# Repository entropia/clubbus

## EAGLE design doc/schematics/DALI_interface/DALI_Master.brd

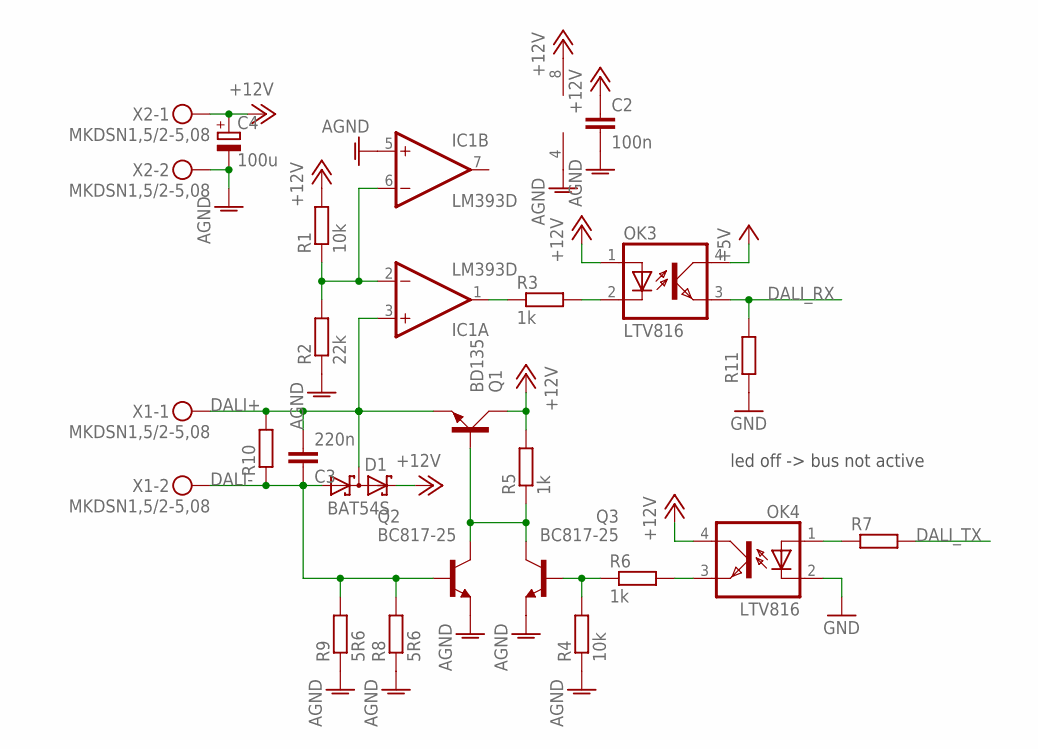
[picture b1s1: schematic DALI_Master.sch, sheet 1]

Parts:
C2: 100n; C0805
C3: 220n; C0805
C4: 100u; E2,5-6
D1: BAT54S; SOT23
IC1: LM393D; SO08
OK3, OK4: LTV816; DIL04
Q1: BD135; TO126AV
Q2, Q3: BC817-25; SOT23-BEC
R1, R4: 10k; R0805
R2: 22k; R0805
R3, R5, R6: 1k; R0805
R7, R10, R11: R-EU_R0805; R0805
R8, R9: 5R6; R1206
X1, X2: MKDSN1,5/2-5,08

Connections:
+5V: OK3.4 (COL); also elsewhere on the board
+12V: C2.1, C4.+, D1.2 (C2), IC1.8 (V+), OK3.1 (A), OK4.4 (COL), Q1.C, R1.2, R5.2, X2.1
AGND: C2.2, C4.-, IC1.4 (V-), IC1.5 (+IN), Q2.E, Q3.E, R2.1, R4.1, R8.1, R9.1, X2.2
DALI+: C3.2, D1.3 (C1A2), IC1.3 (+IN), Q1.E, R10.2, X1.1
DALI-: C3.1, D1.1 (A1), Q2.B, R8.2, R9.2, R10.1, X1.2
DALI_RX: OK3.3 (EMIT), R11.2; also elsewhere on the board
DALI_TX: R7.2; also elsewhere on the board
GND: OK4.2 (C), R11.1; also elsewhere on the board
unnamed: IC1.1 (OUT), R3.1
unnamed: IC1.2 (-IN), IC1.6 (-IN), R1.1, R2.2
unnamed: OK3.2 (C), R3.2
unnamed: Q3.B, R4.2, R6.1
unnamed: OK4.3 (EMIT), R6.2
unnamed: Q1.B, Q2.C, Q3.C, R5.1
unnamed: OK4.1 (A), R7.1

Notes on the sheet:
led off -> bus not active

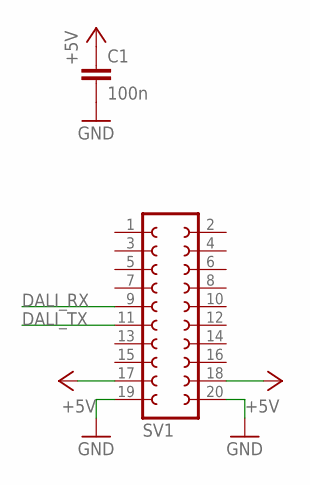
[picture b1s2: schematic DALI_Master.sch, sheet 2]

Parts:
C1: 100n; C0805
SV1: FE10-2

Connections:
+5V: C1.1, SV1.17, SV1.18; also elsewhere on the board
DALI_RX: SV1.9; also elsewhere on the board
DALI_TX: SV1.11; also elsewhere on the board
GND: C1.2, SV1.19, SV1.20; also elsewhere on the board

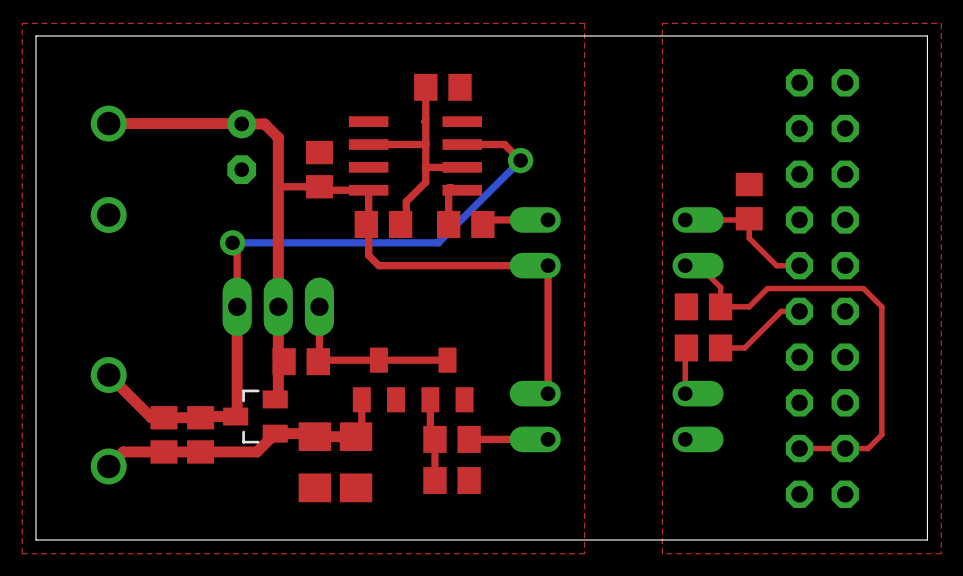
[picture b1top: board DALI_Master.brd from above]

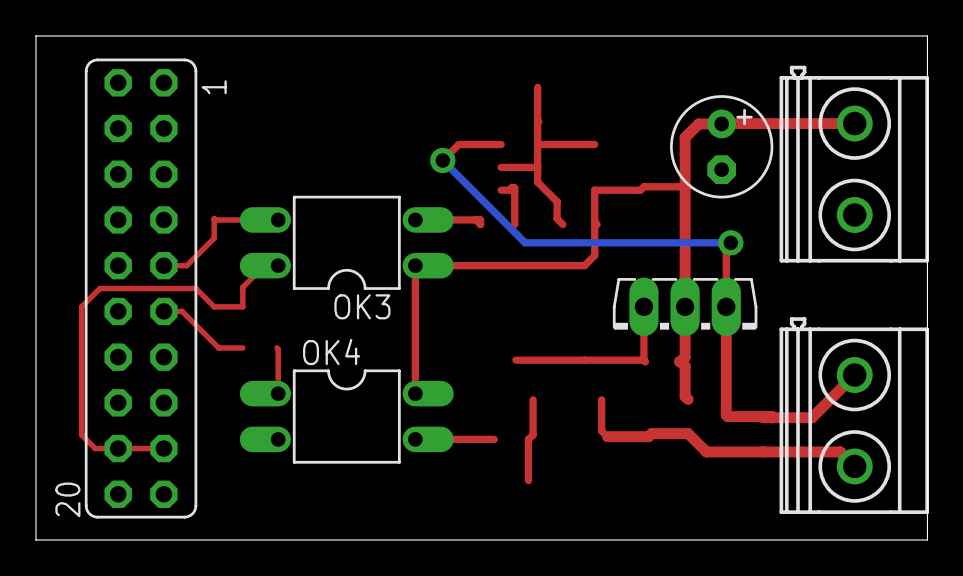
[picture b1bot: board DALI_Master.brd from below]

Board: 2 copper layers, 49.5 x 28.0 mm, 25 parts (7 on the bottom side), 15 nets.

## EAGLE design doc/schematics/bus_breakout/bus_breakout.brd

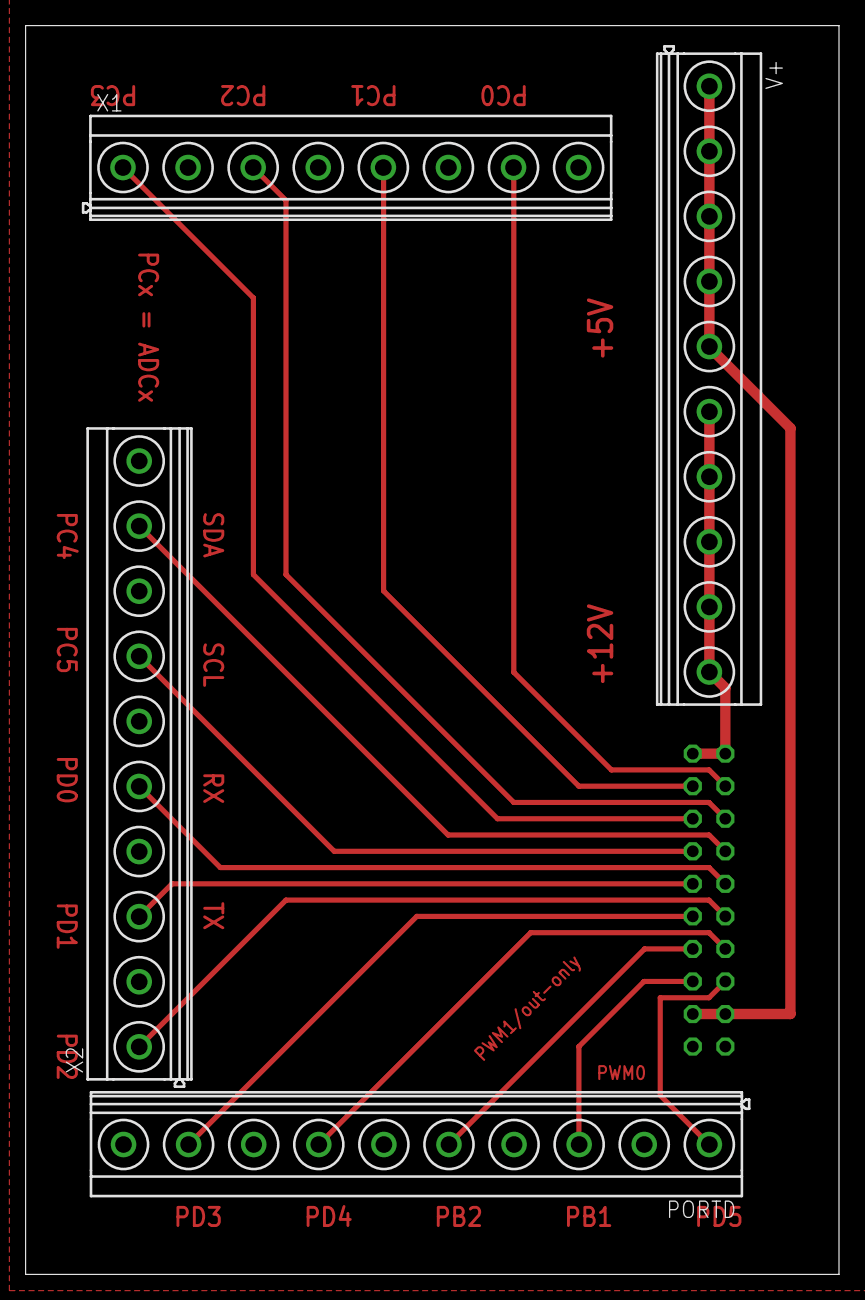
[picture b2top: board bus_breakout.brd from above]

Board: 2 copper layers, 63.5 x 97.5 mm, 5 parts (1 on the bottom side), 17 nets.

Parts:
PORTD: MKDSN1,5/10-5,08
SV2: FE10-2
V+: MKDSN1,5/10-5,08
X1: MKDSN1,5/8-5,08
X2: MKDSN1,5/10-5,08

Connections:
+5V: SV2.17, SV2.18, V+.1, V+.2, V+.3, V+.4, V+.5
+12V: SV2.1, SV2.2, V+.6, V+.7, V+.8, V+.9, V+.10
GND: PORTD.2, PORTD.4, PORTD.6, PORTD.8, PORTD.10, SV2.19, SV2.20, X1.2, X1.4, X1.6, X1.8, X2.2, X2.4, X2.6, X2.8, X2.10
PC0/ADC0: SV2.4, X1.7
PC1/ADC1: SV2.3, X1.5
PC2/ADC2: SV2.6, X1.3
PC3/ADC3: SV2.5, X1.1
PC4/ADC4/SDA: SV2.8, X2.9
PC5/ADC5/SCL: SV2.7, X2.7
PD0/RX: SV2.10, X2.5
PD1/TX: SV2.9, X2.3
PD2: SV2.12, X2.1
PD3: PORTD.9, SV2.11
PD4: PORTD.7, SV2.14
PD5: PORTD.1, SV2.16
PWM0: PORTD.3, SV2.15
PWM1: PORTD.5, SV2.13

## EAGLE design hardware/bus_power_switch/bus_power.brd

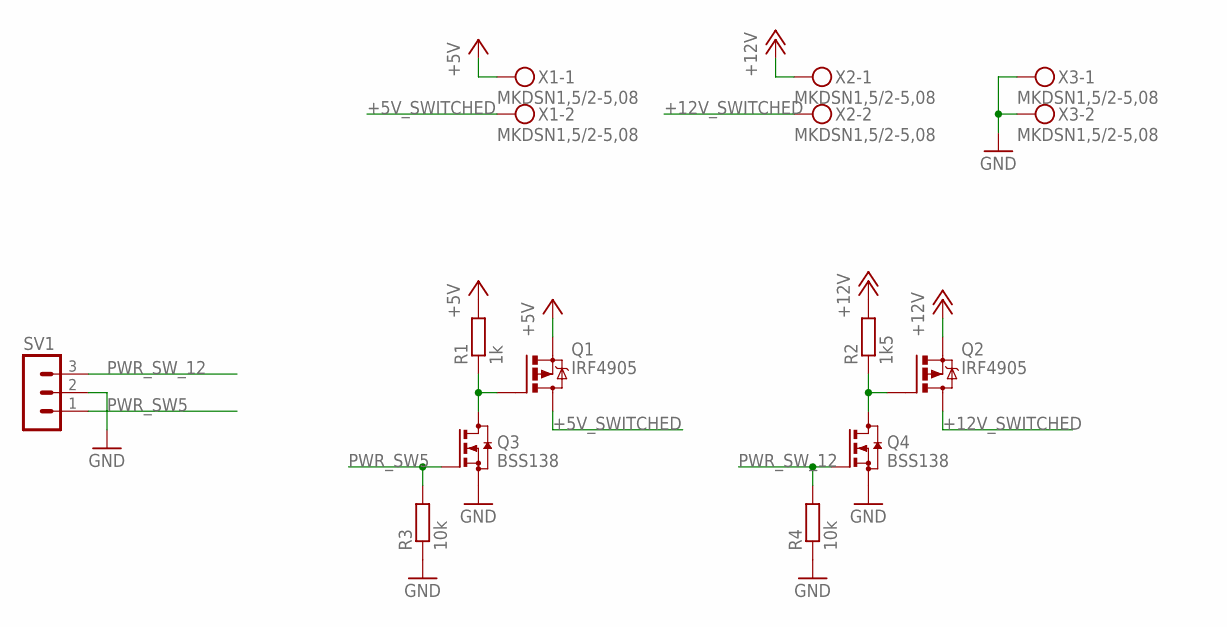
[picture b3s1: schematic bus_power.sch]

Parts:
Q1, Q2: IRF4905; TO220BV
Q3, Q4: BSS138; SOT23
R1: 1k; R0805
R2: 1k5; R0805
R3, R4: 10k; R0805
SV1: MA03-1
X1, X2, X3: MKDSN1,5/2-5,08

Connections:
+5V: Q1.S, R1.2, X1.1
+5V_SWITCHED: Q1.D, X1.2
+12V: Q2.S, R2.2, X2.1
+12V_SWITCHED: Q2.D, X2.2
G5: Q1.G, Q3.3 (D), R1.1
G12: Q2.G, Q4.3 (D), R2.1
GND: Q3.2 (S), Q4.2 (S), R3.1, R4.1, SV1.2, X3.1, X3.2
PWR_SW5: Q3.1 (G), R3.2, SV1.1
PWR_SW_12: Q4.1 (G), R4.2, SV1.3

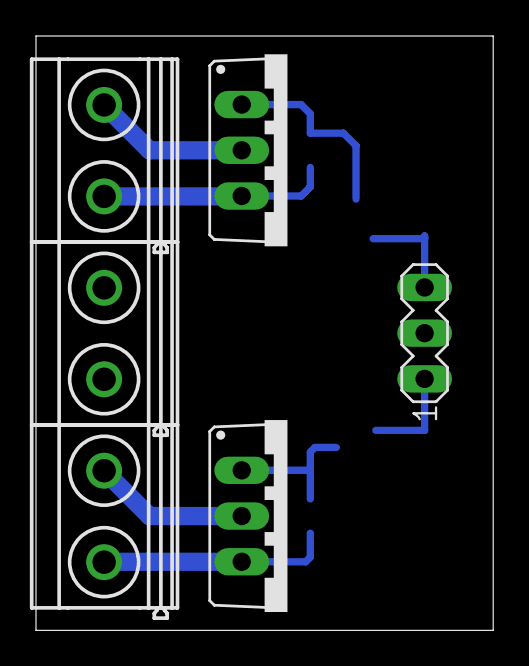
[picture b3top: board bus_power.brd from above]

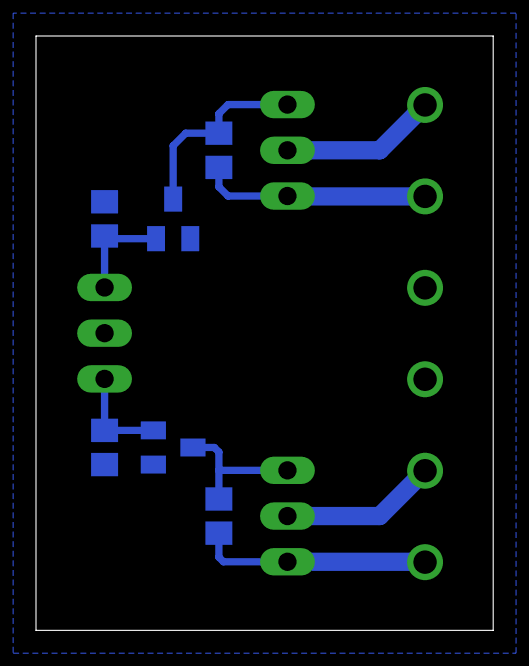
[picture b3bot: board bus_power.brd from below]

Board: 2 copper layers, 25.4 x 33.0 mm, 12 parts (6 on the bottom side), 9 nets.

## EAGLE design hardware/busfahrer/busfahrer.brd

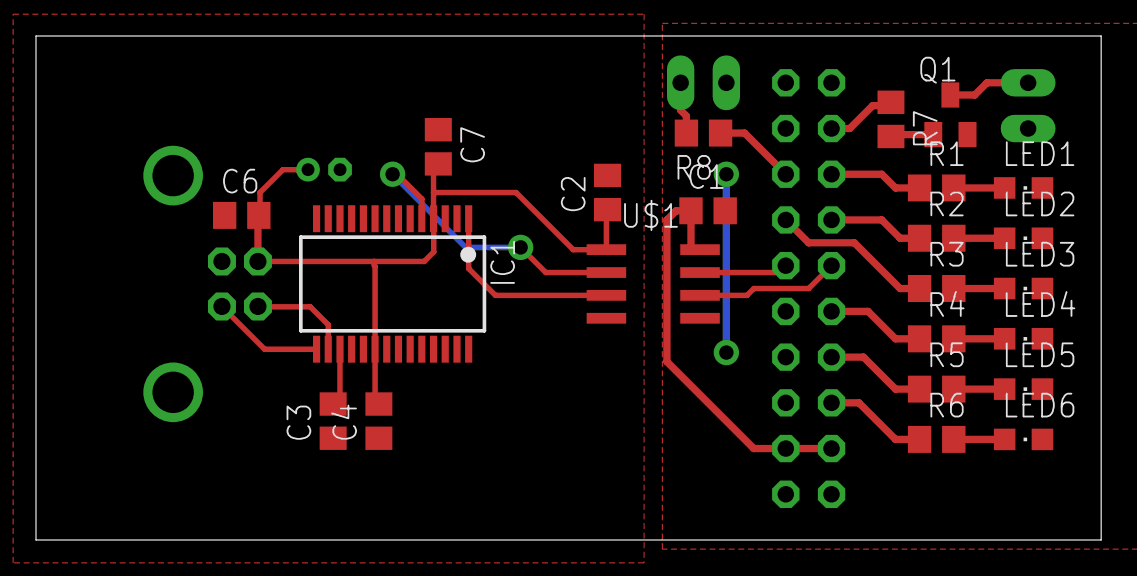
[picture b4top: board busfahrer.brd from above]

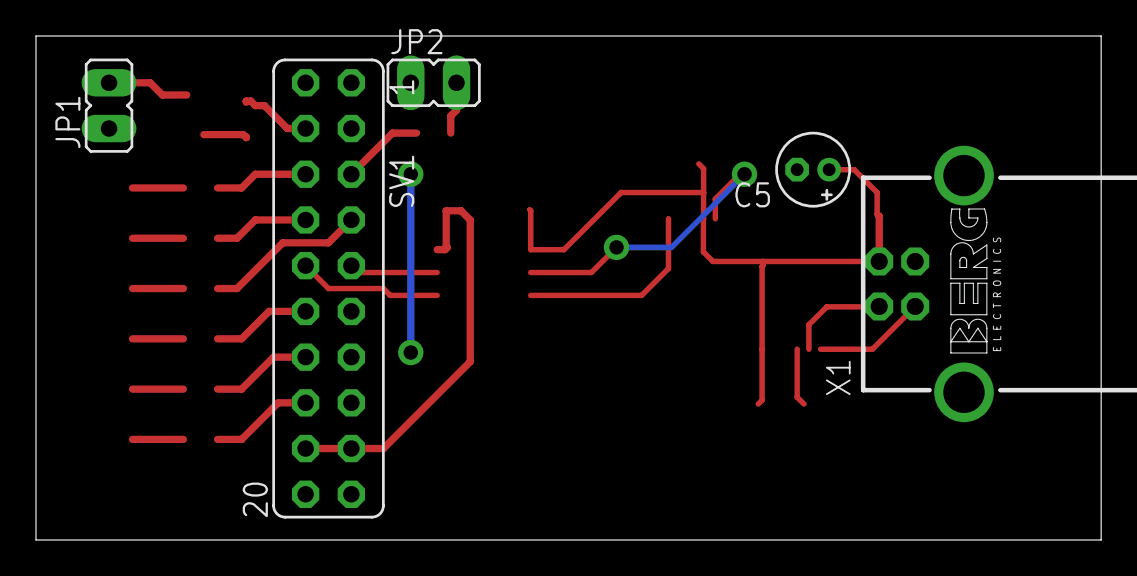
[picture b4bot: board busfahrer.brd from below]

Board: 2 copper layers, 59.2 x 28.0 mm, 28 parts (5 on the bottom side), 28 nets.

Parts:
C1, C2, C3, C4, C7: 100n; C0805
C5: 10u; E1,8-4
C6: 10n; C0805
IC1: FT232RL; SSOP28
JP1, JP2: JP1
LED1, LED2, LED3, LED4, LED5, LED6: CHIPLED_0805
Q1: BC848CSMD; SOT23
R1, R2, R3, R4, R5, R6: 470; R0805
R7, R8: 10k; R0805
SV1: FE10-2
U$1: ADUM3211; SO8
X1: PN61729-S

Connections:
3V3: C3.2, IC1.17
!PS_ON: JP1.2, Q1.3
+5V: C2.1, C4.2, C5.+, C6.2, C7.2, IC1.4, IC1.20, U$1.1, X1.1
GND: C2.2, C3.1, C4.1, C5.-, C6.1, C7.1, IC1.7, IC1.18, IC1.21, IC1.25, IC1.26, U$1.4, X1.4, X1.S1, X1.S2
GNDI: C1.2, JP1.1, JP2.1, LED1.C, LED2.C, LED3.C, LED4.C, LED5.C, LED6.C, Q1.2, SV1.19, SV1.20, U$1.5
LED_1: R1.1, SV1.6
LED_2: R2.1, SV1.8
LED_3: R3.1, SV1.7
LED_4: R4.1, SV1.12
LED_5: R5.1, SV1.14
LED_6: R6.1, SV1.16
MOD_RX: SV1.10, U$1.6
MOD_TX: SV1.9, U$1.7
unnamed: Q1.1, R7.2
unnamed: R7.1, SV1.4
unnamed: R8.1, SV1.5
unnamed: LED1.A, R1.2
unnamed: LED2.A, R2.2
unnamed: LED3.A, R3.2
unnamed: LED4.A, R4.2
unnamed: LED5.A, R5.2
unnamed: LED6.A, R6.2
PWR_OK: JP2.2, R8.2
USB_DM: IC1.16, X1.2
USB_DP: IC1.15, X1.3
USB_RX: IC1.5, U$1.2
USB_TX: IC1.1, U$1.3
VCC: C1.1, SV1.17, SV1.18, U$1.8
